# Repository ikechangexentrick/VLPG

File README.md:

# VLPG
Low pass gate using vactrols

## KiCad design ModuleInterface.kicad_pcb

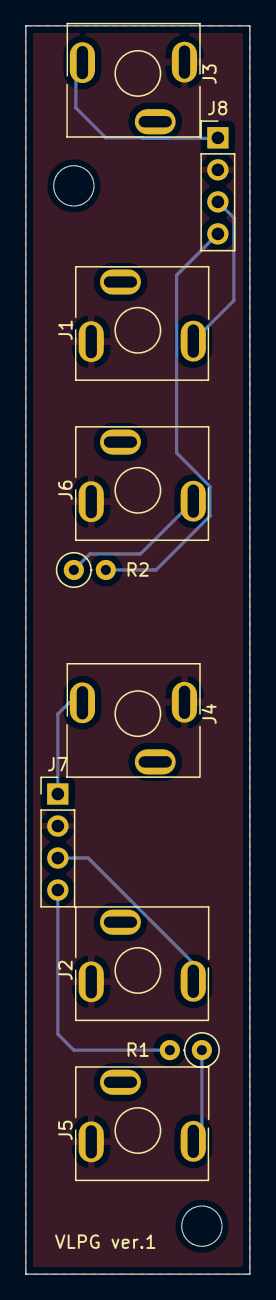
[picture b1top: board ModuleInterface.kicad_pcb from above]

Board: 2 copper layers, 17.8 x 99.1 mm, 16 parts (0 on the bottom side), 9 nets.

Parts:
1, 2#2: annotation_3.5mm_jack_out_bottom
1#2, 2: annotation_3.5mm_jack_in
CV1, CV2: annotation_3.5mm_jack_in
J1: in1; MJ-355_3.5mm_mono_jack
J2: in2; MJ-355_3.5mm_mono_jack
J3: cv1; MJ-355_3.5mm_mono_jack
J4: cv2; MJ-355_3.5mm_mono_jack
J5: out2; MJ-355_3.5mm_mono_jack
J6: out1; MJ-355_3.5mm_mono_jack
J7: conn2; PinHeader_1x04_P2.54mm_Vertical
J8: conn1; PinHeader_1x04_P2.54mm_Vertical
R1, R2: 1k; R_Axial_DIN0207_L6.3mm_D2.5mm_P2.54mm_Vertical

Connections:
/Interface/cv1: J3.T, J8.1
/Interface/cv2: J4.T, J7.1
/Interface/in1: J1.T, J8.3
/Interface/in2: J2.T, J7.3
/Interface/out1: J8.4, R2.2
/Interface/out2: J7.4, R1.2
GND: J1.S, J2.S, J3.S, J4.S, J5.S, J6.S, J7.2, J8.2
unnamed: J5.T, R1.1
unnamed: J6.T, R2.1

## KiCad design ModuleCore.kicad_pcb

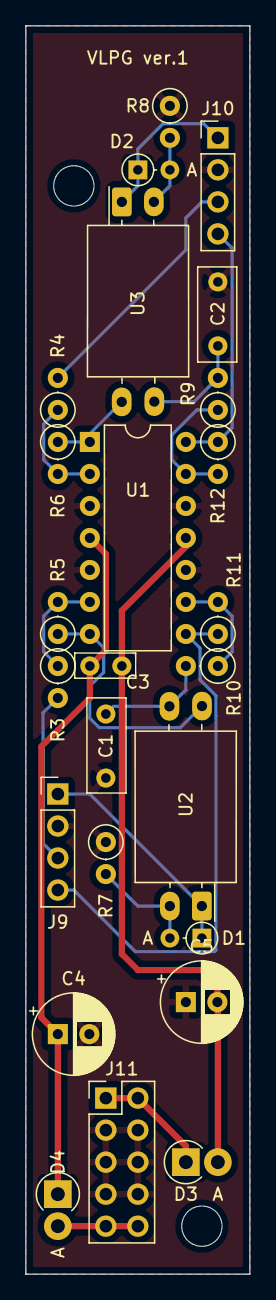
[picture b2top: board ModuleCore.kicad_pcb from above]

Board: 2 copper layers, 17.8 x 99.1 mm, 25 parts (0 on the bottom side), 21 nets.

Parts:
C1, C2: 0.047u; C_Axial_L4.8mm_D3.1mm_P5.08mm_Horizontal
C3: 0.1u; C_Axial_L4.8mm_D2.0mm_P2.54mm_Horizontal
C4, C5: 100u; CP_Radial_D6.3mm_P2.50mm
D1, D2: 1N4148; D_DO-34_SOD68_P2.54mm_Vertical_AnodeUp
D3, D4: 1N5818; D_DO-41_SOD81_P2.54mm_Vertical_AnodeUp
J9: conn2; PinHeader_1x04_P2.54mm_Vertical
J10: conn1; PinHeader_1x04_P2.54mm_Vertical
J11: power_bus; PinHeader_2x05_P2.54mm_Vertical
R3, R4, R5, R6, R9, R10, R11, R12: 10k; R_Axial_DIN0207_L6.3mm_D2.5mm_P2.54mm_Vertical
R7, R8: 220; R_Axial_DIN0207_L6.3mm_D2.5mm_P2.54mm_Vertical
U1: TL074; DIP-14_W7.62mm
U2, U3: VTL5C3

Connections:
+12V: C3.1, C4.1, D4.1, U1.4
-12V: C3.2, C5.2, D3.2, U1.11
/Core/cv1: D2.1, J10.1, U3.1
/Core/cv2: D1.1, J9.1, U2.1
/Core/in1: J10.3, R4.2
/Core/in2: J9.3, R3.2
/Core/out1: J10.4, R12.1, U1.14
/Core/out2: J9.4, R11.1, U1.8
GND: C1.2, C2.2, C4.2, C5.1, J9.2, J10.2, J11.3, J11.4, J11.5, J11.6, J11.7, J11.8, R7.1, R8.1, U1.3, U1.5, U1.10, U1.12
unnamed: C1.1, R10.2, U2.3
unnamed: C2.1, R9.2, U3.3
unnamed: D1.2, R7.2, U2.2
unnamed: D2.2, R8.2, U3.2
unnamed: D3.1, J11.1, J11.2
unnamed: D4.2, J11.9, J11.10
unnamed: R3.1, R5.2, U1.6
unnamed: R4.1, R6.2, U1.2
unnamed: R5.1, U1.7, U2.4
unnamed: R6.1, U1.1, U3.4
unnamed: R10.1, R11.2, U1.9
unnamed: R9.1, R12.2, U1.13

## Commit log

2022-09-08 Low pass gate using vactrols, "VLPG".
